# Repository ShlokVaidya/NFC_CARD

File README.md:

# NFC_CARD

Custom NFC Card

Schematic

PCB

3D

Order

BOM

Requesting a grant of $23

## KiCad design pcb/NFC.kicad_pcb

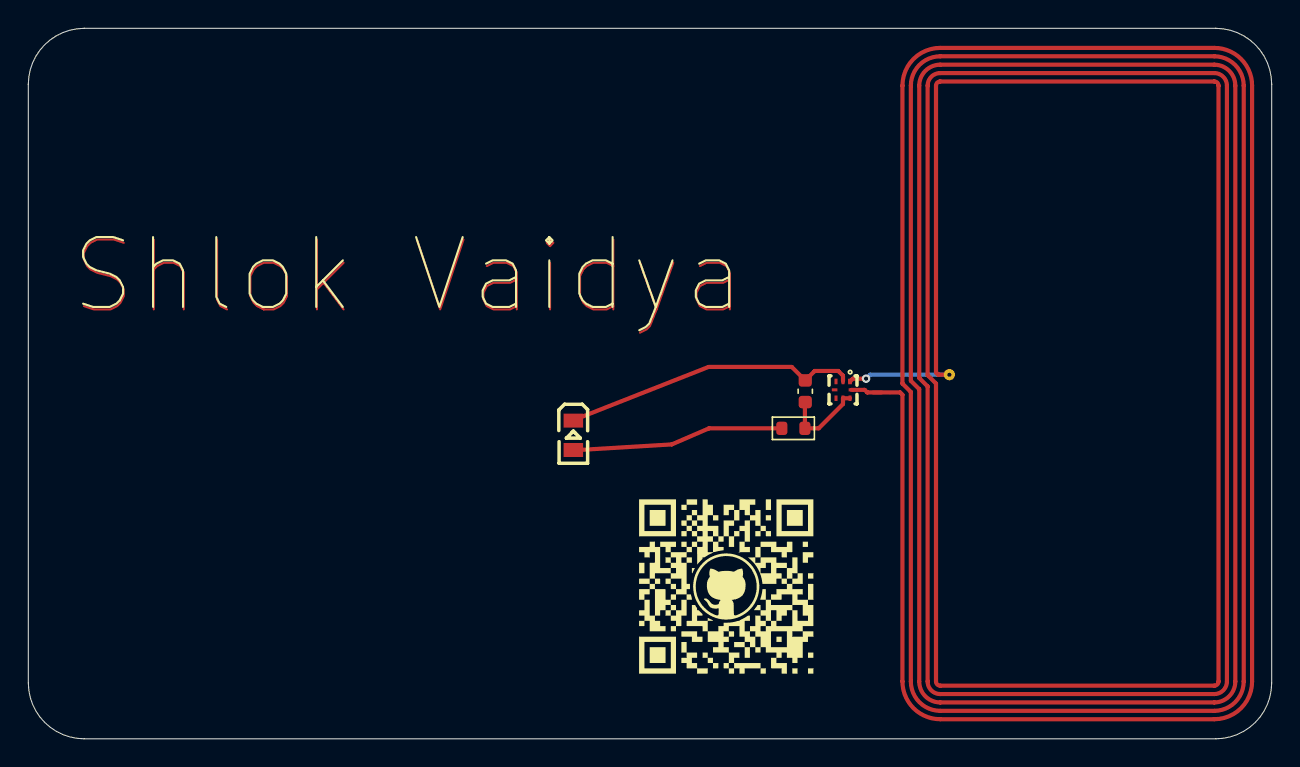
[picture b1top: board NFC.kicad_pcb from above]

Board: 2 copper layers, 88.9 x 50.8 mm, 5 parts (0 on the bottom side), 3 nets.

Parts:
C1: 220nF; C_0603_1608Metric
L1: 25X48MM_NFC_ANTENNA
LED1: 17-21SUYC/TR8; LED0805-R-RD
R1: 47; R_0603_1608Metric
U1: NT3H2111W0FHKH; XQFN-8_L1.6-W1.6-P0.50-BL_NT3H2111W0FHKH

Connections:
unnamed: LED1.1 (+), R1.1
unnamed: C1.1, LED1.2 (-), U1.2 (VSS)
unnamed: C1.2, R1.2, U1.6 (VCC), U1.7 (VOUT)

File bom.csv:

Designator,Footprint,Quantity,Value,LCSC Part #
C1,0603,1,220nF,C21120
L1,25X48MM_NFC_ANTENNA,1,25X48MM_NFC_ANTENNA,
LED1,LED0805-R-RD,1,17-21SUYC/TR8,C2296
R1,0603,1,47,C23182
U1,XQFN-8_L1.6-W1.6-P0.50-BL_NT3H2111W0FHKH,1,NT3H2111W0FHKH,C710403

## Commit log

2025-12-02 NFC v2.0
2026-01-03 Enhance README with NFC and YouTube images
    Added images for NFC and YouTube links to README.
